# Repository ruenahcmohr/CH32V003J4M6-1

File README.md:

# CH32V003 breakout

The intent of this board is something that can have wires soldered to the pads and be glued into simple devices.
It breaks out all the ch32 pins, has a decoupling cap, a power LED and a programming header.

I soldered the test unit as a SIP module.

As normal for me, I have removed most of the silk screen. 
Be careful of where pin 1 of the ch32 goes. The edge pins are numbered 1:1 with the ch32.

The LED is reverse mounted to shine thru the hole. I wanted to try this on a manufactured pcb, 
but the hole is small and it didn't work out as awesome as it does on protoboard.

I used a 3.3k resistor for the LED. I reccomend 2.2k, but with bright LEDs 10k is probably fine.

The capacitor is decoupling, so any 0805 between 0.01uF and 3F should do.

I included the gerbers, but jokes on you, kicad didn't backport their versions far enough and I'm using 
5.1.9 haha!

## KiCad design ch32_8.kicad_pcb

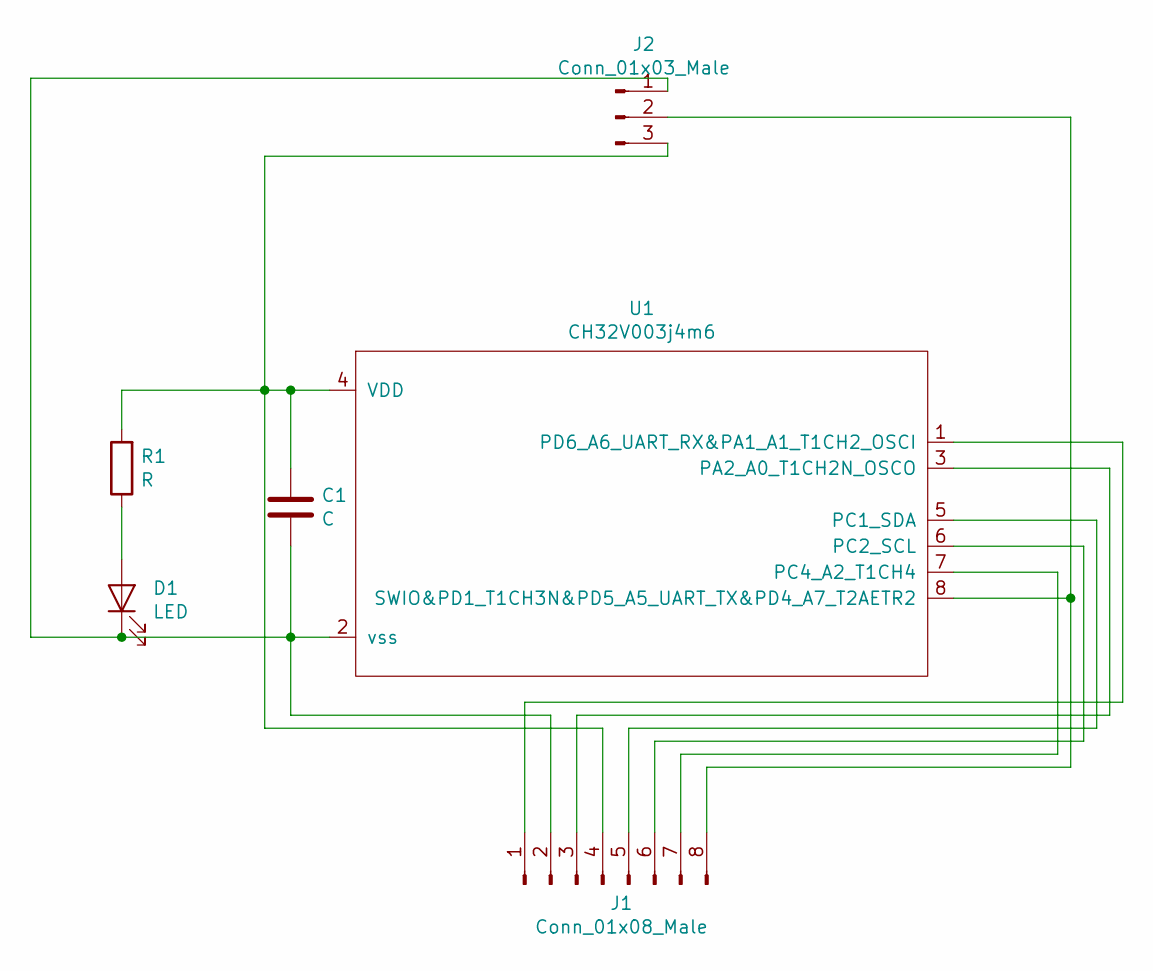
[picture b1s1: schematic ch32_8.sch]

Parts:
C1: C; C_0805_2012Metric_Pad1.15x1.40mm_HandSolder
D1: LED; LED_0805_2012Metric_Pad1.15x1.40mm_HandSolder
J1: Conn_01x08_Male; PinHeader_1x08_P2.54mm_Vertical
J2: Conn_01x03_Male; PinSocket_1x03_P2.54mm_Vertical
R1: R; R_0805_2012Metric_Pad1.15x1.40mm_HandSolder
U1: CH32V003j4m6; SOIC-8_3.9x4.9mm_P1.27mm

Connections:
unnamed: C1.1, J1.4, J2.3, R1.2, U1.4 (VDD)
unnamed: C1.2, D1.1 (K), J1.2, J2.1, U1.2 (vss)
unnamed: D1.2 (A), R1.1
unnamed: J1.1, U1.1 (PD6_A6_UART_RX&PA1_A1_T1CH2_OSCI)
unnamed: J1.3, U1.3 (PA2_A0_T1CH2N_OSCO)
unnamed: J1.5, U1.5 (PC1_SDA)
unnamed: J1.6, U1.6 (PC2_SCL)
unnamed: J1.7, U1.7 (PC4_A2_T1CH4)
unnamed: J1.8, J2.2, U1.8 (SWIO&PD1_T1CH3N&PD5_A5_UART_TX&PD4_A7_T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)

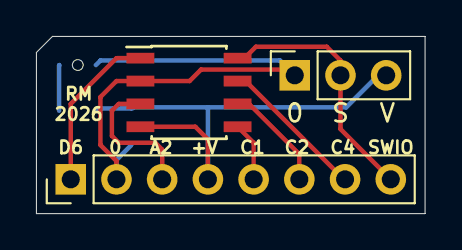
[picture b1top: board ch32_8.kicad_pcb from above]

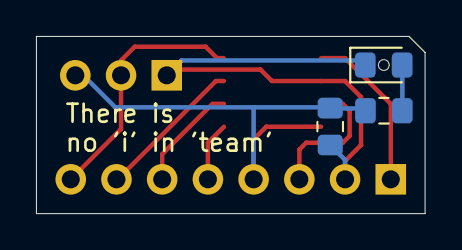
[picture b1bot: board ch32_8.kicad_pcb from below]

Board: 2 copper layers, 21.6 x 9.8 mm, 6 parts (3 on the bottom side), 9 nets.

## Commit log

2026-03-06 adding files
